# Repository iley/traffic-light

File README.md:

# Tabletop traffic light

This is a hacked toy traffic light. It uses ESP-8266.

## What it looks like

## Internals

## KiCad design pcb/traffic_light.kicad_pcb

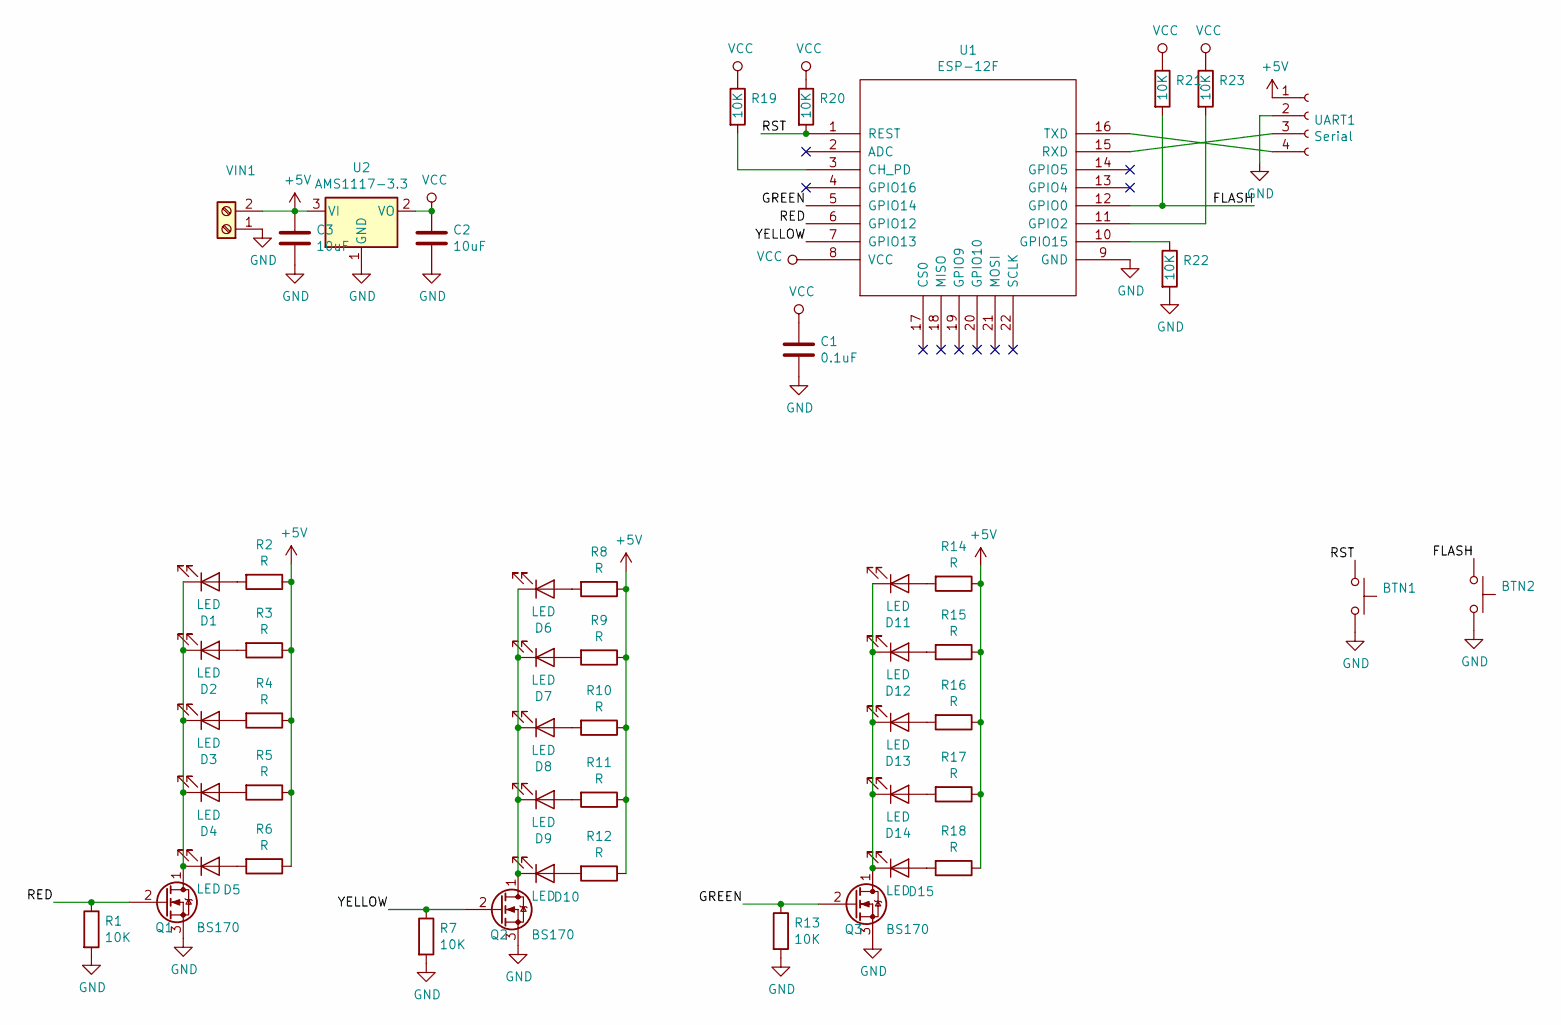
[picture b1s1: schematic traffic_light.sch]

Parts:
BTN1: RESET; SW_PUSH_6mm
BTN2: FLASH; SW_PUSH_6mm
C1: 0.1uF; C_1206_3216Metric
C2, C3: 10uF; C_1206_3216Metric
D1, D2, D3, D4, D5, D6, D7, D8, D9, D10, D11, D12, D13, D14, D15: LED; LED_D5.0mm
Q1, Q2, Q3: BS170; TO-92_Inline
R1, R7, R13, R19, R20, R21, R22, R23: 10K; R_1206_3216Metric_Pad1.42x1.75mm_HandSolder
R2, R3, R4, R5, R6, R8, R9, R10, R11, R12, R14, R15, R16, R17, R18: R; R_1206_3216Metric_Pad1.42x1.75mm_HandSolder
U1: ESP-12F; ESP-12E_SMD
U2: AMS1117-3.3; SOT-223-3_TabPin2
UART1: Serial; PinHeader_1x04_P2.54mm_Vertical
VIN1: Power; PinHeader_1x02_P2.54mm_Vertical

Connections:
+5V: C3.1, R2.1, R3.1, R4.1, R5.1, R6.1, R8.1, R9.1, R10.1, R11.1, R12.1, R14.1, R15.1, R16.1, R17.1, R18.1, U2.3 (VI), UART1.1, VIN1.2
/FLASH: BTN2.1, R21.2, U1.12 (GPIO0)
/GREEN: Q3.2 (G), R13.1, U1.5 (GPIO14)
/RED: Q1.2 (G), R1.1, U1.6 (GPIO12)
/RST: BTN1.1, R20.2, U1.1 (REST)
/YELLOW: Q2.2 (G), R7.1, U1.7 (GPIO13)
GND: BTN1.2, BTN2.2, C1.2, C2.2, C3.2, Q1.3 (S), Q2.3 (S), Q3.3 (S), R1.2, R7.2, R13.2, R22.2, U1.9 (GND), U2.1 (GND), UART1.2, VIN1.1
unnamed: D1.1 (K), D2.1 (K), D3.1 (K), D4.1 (K), D5.1 (K), Q1.1 (D)
unnamed: D1.2 (A), R2.2
unnamed: D2.2 (A), R3.2
unnamed: D3.2 (A), R4.2
unnamed: D4.2 (A), R5.2
unnamed: D5.2 (A), R6.2
unnamed: D6.2 (A), R8.2
unnamed: D7.2 (A), R9.2
unnamed: D8.2 (A), R10.2
unnamed: D9.2 (A), R11.2
unnamed: D6.1 (K), D7.1 (K), D8.1 (K), D9.1 (K), D10.1 (K), Q2.1 (D)
unnamed: D10.2 (A), R12.2
unnamed: D11.1 (K), D12.1 (K), D13.1 (K), D14.1 (K), D15.1 (K), Q3.1 (D)
unnamed: D11.2 (A), R14.2
unnamed: D12.2 (A), R15.2
unnamed: D13.2 (A), R16.2
unnamed: D14.2 (A), R17.2
unnamed: D15.2 (A), R18.2
unnamed: R19.2, U1.3 (CH_PD)
unnamed: R22.1, U1.10 (GPIO15)
unnamed: R23.2, U1.11 (GPIO2)
unnamed: U1.15 (RXD), UART1.3
unnamed: U1.16 (TXD), UART1.4
VCC: C1.1, C2.1, R19.1, R20.1, R21.1, R23.1, U1.8 (VCC), U2.2 (VO)

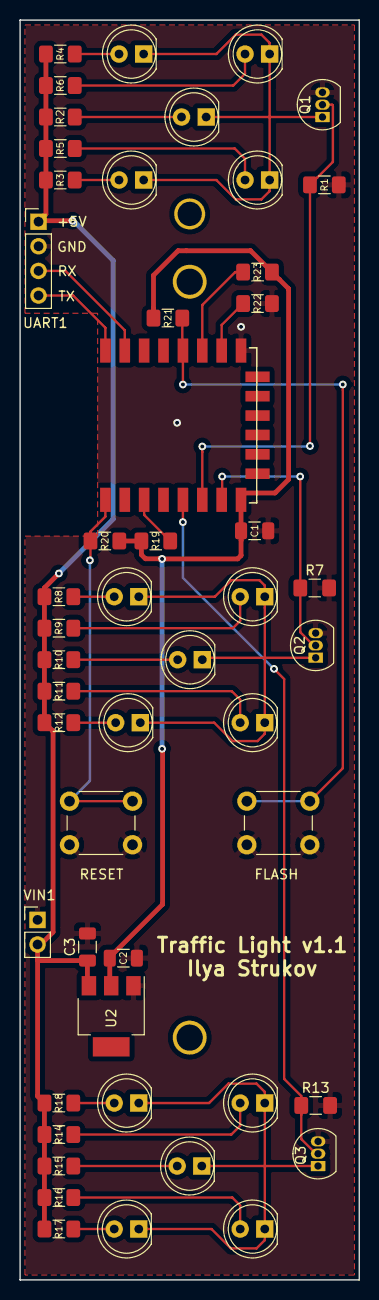
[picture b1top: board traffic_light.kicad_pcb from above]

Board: 2 copper layers, 35.0 x 130.0 mm, 50 parts (0 on the bottom side), 31 nets.

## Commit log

2018-12-05 first take on a schematic
2018-12-05 start assigning footprints
2018-12-05 start laying out the PCB
2018-12-06 laying out PCB
2018-12-08 place all components on the board
2018-12-08 route everything
2018-12-08 minor layout changes
2018-12-08 final touches
2018-12-09 simple firmware using MongooseOS
2018-12-09 add an example script for controlling the device remotely
2018-12-09 add firmware readme
2018-12-09 formatting
2019-01-13 blink lights on startup
2019-01-14 change default device name
2019-01-14 add build status script
2019-01-14 add makefile
2019-01-14 make code work in lambda
2019-01-15 turn on all lights on error
2019-04-28 Add README
2019-04-28 Fix a bug in shadow handling
2019-05-01 Minor PCB improvements
2019-08-30 add a script for checking jenkins status
2022-04-29 I dunno ¯\_(ツ)_/¯
2023-05-22 Bump requests from 2.21.0 to 2.31.0 in /backend
    Bumps [requests](https://github.com/psf/requests) from 2.21.0 to 2.31.0.
    - [Release notes](https://github.com/psf/requests/releases)
    - [Changelog](https://github.com/psf/requests/blob/main/HISTORY.md)
    - [Commits](https://github.com/psf/requests/compare/v2.21.0...v2.31.0)
    ---
    updated-dependencies:
2023-05-22 Bump requests from 2.21.0 to 2.31.0 in /backend/bamboo
    Bumps [requests](https://github.com/psf/requests) from 2.21.0 to 2.31.0.
    - [Release notes](https://github.com/psf/requests/releases)
    - [Changelog](https://github.com/psf/requests/blob/main/HISTORY.md)
    - [Commits](https://github.com/psf/requests/compare/v2.21.0...v2.31.0)
    ---
    updated-dependencies:
2024-05-20 --- updated-dependencies: - dependency-name: requests dependency-type: direct:production ...
2025-06-09 Bump requests from 2.32.0 to 2.32.4 in /backend
    Bumps [requests](https://github.com/psf/requests) from 2.32.0 to 2.32.4.
    - [Release notes](https://github.com/psf/requests/releases)
    - [Changelog](https://github.com/psf/requests/blob/main/HISTORY.md)
    - [Commits](https://github.com/psf/requests/compare/v2.32.0...v2.32.4)
    ---
    updated-dependencies:
2026-03-25 Bump requests from 2.32.4 to 2.33.0 in /backend
    Bumps [requests](https://github.com/psf/requests) from 2.32.4 to 2.33.0.
    - [Release notes](https://github.com/psf/requests/releases)
    - [Changelog](https://github.com/psf/requests/blob/main/HISTORY.md)
    - [Commits](https://github.com/psf/requests/compare/v2.32.4...v2.33.0)
    ---
    updated-dependencies:
2026-03-26 Bump requests from 2.32.4 to 2.33.0 in /backend/jenkins
    Bumps [requests](https://github.com/psf/requests) from 2.32.4 to 2.33.0.
    - [Release notes](https://github.com/psf/requests/releases)
    - [Changelog](https://github.com/psf/requests/blob/main/HISTORY.md)
    - [Commits](https://github.com/psf/requests/compare/v2.32.4...v2.33.0)
    ---
    updated-dependencies:
2026-03-26 Bump requests from 2.32.4 to 2.33.0 in /backend/bamboo
    Bumps [requests](https://github.com/psf/requests) from 2.32.4 to 2.33.0.
    - [Release notes](https://github.com/psf/requests/releases)
    - [Changelog](https://github.com/psf/requests/blob/main/HISTORY.md)
    - [Commits](https://github.com/psf/requests/compare/v2.32.4...v2.33.0)
    ---
    updated-dependencies:
